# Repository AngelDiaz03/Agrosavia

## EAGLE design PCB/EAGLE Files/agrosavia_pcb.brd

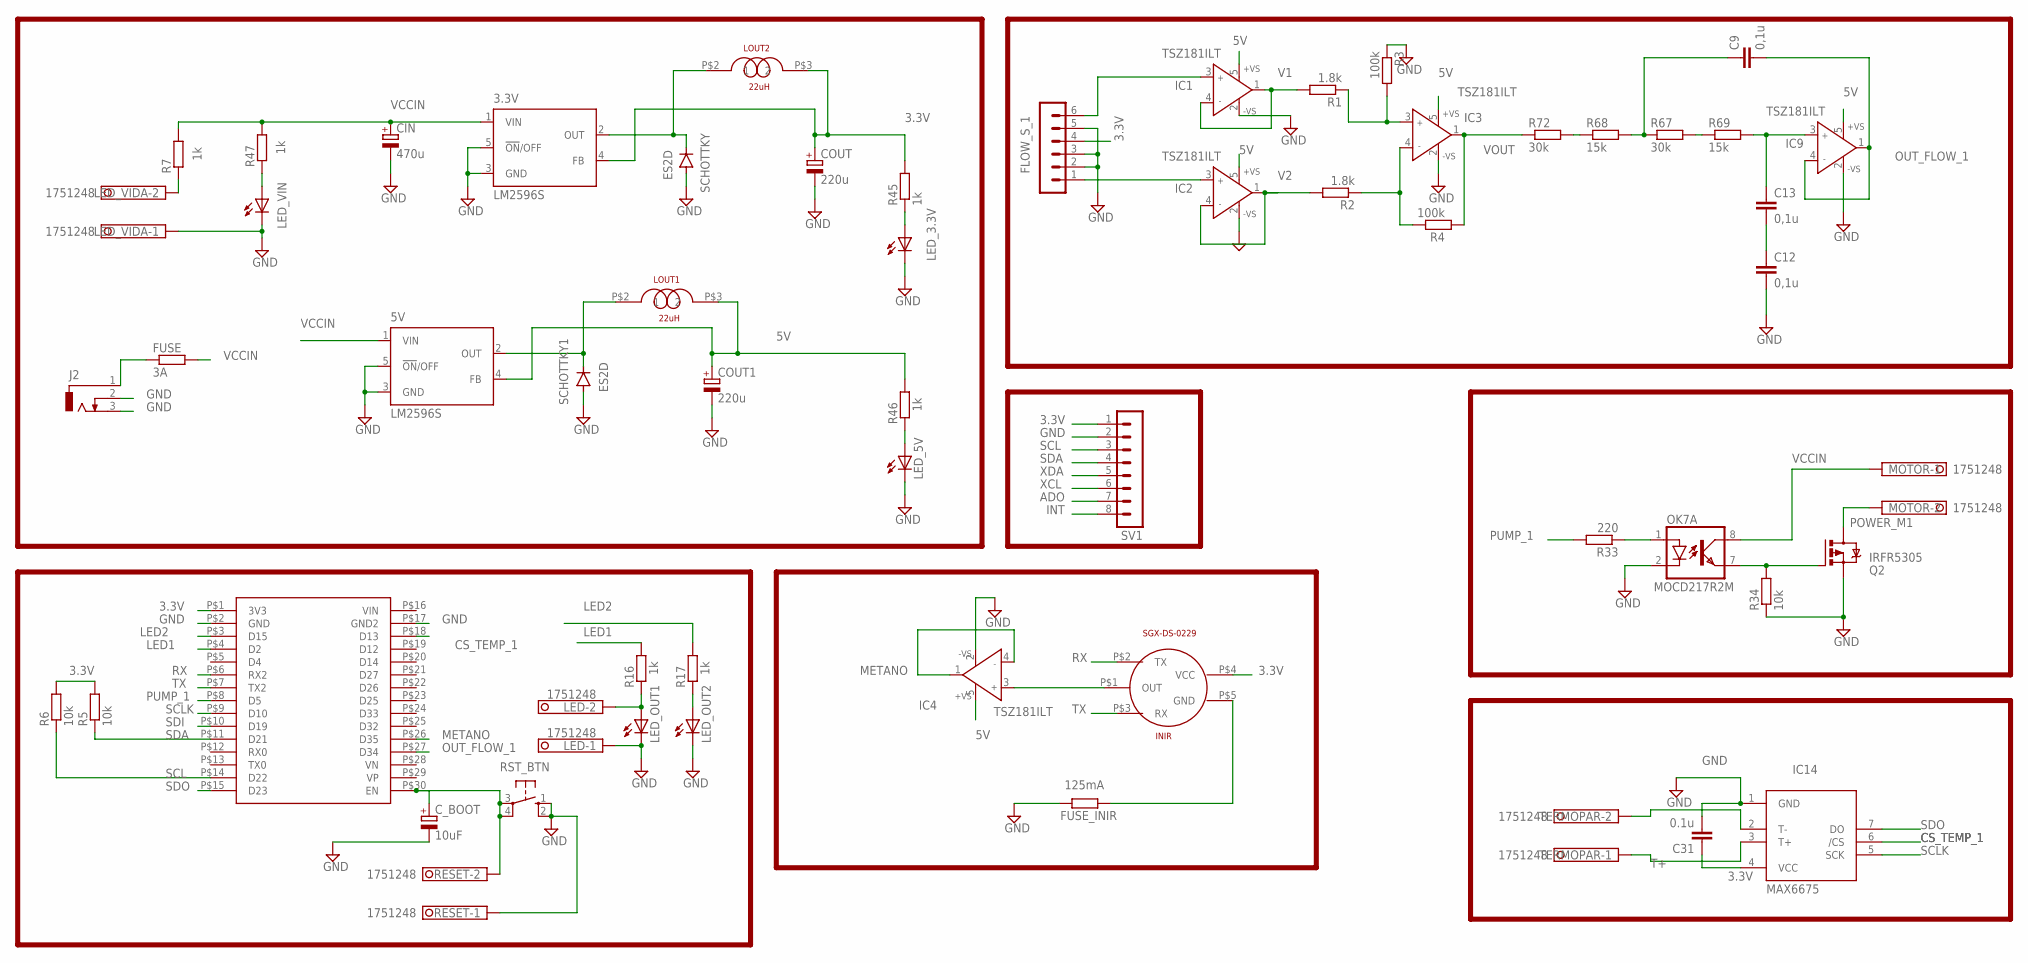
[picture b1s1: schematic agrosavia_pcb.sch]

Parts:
3.3V, 5V: LM2596S; TO263-5
C9, C12, C13: 0,1u; C0805
C31: 0.1u; C0805
CIN: 470u; SANYO-OSCON_SMD_F12
COUT, COUT1: 220u; UD-10X10_NICHICON
C_BOOT: 10uF; SANYO-OSCON_SMD_B6
ESP32DEVKITV1: ESP32
FLOW_S_1: MA06-1
FUSE: 3A; R1206
FUSE_INIR: 125mA; R0402
IC1, IC2, IC3, IC4, IC9: TSZ181ILT; SOT23-5
IC14: MAX6675; SO08
J2: DCJ0303
LED: 1751248
LED_3.3V, LED_5V: LED_E; LED_1206
LED_OUT1, LED_OUT2: LED_E; LED_1206
LED_VIDA: 1751248
LED_VIN: LED_E; LED_1206
LOUT1, LOUT2: 22uH; SRP1038A
MOTOR: 1751248
OK7: MOCD217R2M; SOIC08
Q2: IRFR5305; D-PAK_TO252AA
R1, R2: 1.8k; R0805
R3, R4: 100k; R0805
R5, R6, R34: 10k; R1206
R7, R16, R17, R45, R46, R47: 1k; R0805
R33: 220; R0603
R67, R72: 30k; R0805
R68, R69: 15k; R0805
RESET: 1751248
RST_BTN: 10-XX; B3F-10XX
SCHOTTKY, SCHOTTKY1: ES2D; SMB
SGX-DS-0229: INIR
SV1: MA08-1
TERMOPAR: 1751248

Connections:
3.3V: 3.3V.4 (FB), C31.1, COUT.+, ESP32DEVKITV1.P$1 (3V3), FLOW_S_1.4, IC14.4 (VCC), LOUT2.P$3 (2), R5.2, R6.2, R45.2, SGX-DS-0229.P$4 (VCC), SV1.1
5V: 5V.4 (FB), COUT1.+, IC1.5 (+VS), IC2.5 (+VS), IC3.5 (+VS), IC4.5 (+VS), IC9.5 (+VS), LOUT1.P$3 (2), R46.2
ADO: SV1.7
CS_TEMP_1: ESP32DEVKITV1.P$18 (D13), IC14.6 (/CS)
GND: 3.3V.3 (GND), 3.3V.5 (!ON!/OFF), 5V.3 (GND), 5V.5 (!ON!/OFF), C12.2, C31.2, CIN.-, COUT.-, COUT1.-, C_BOOT.-, ESP32DEVKITV1.P$2 (GND), ESP32DEVKITV1.P$17 (GND2), FLOW_S_1.2, FLOW_S_1.3, FLOW_S_1.5, FUSE_INIR.2, IC1.2 (-VS), IC2.2 (-VS), IC3.2 (-VS), IC4.2 (-VS), IC9.2 (-VS), IC14.1 (GND), J2.2, J2.3, LED.1, LED_3.3V.C, LED_5V.C, LED_OUT1.C, LED_OUT2.C, LED_VIDA.1, LED_VIN.C, OK7.2 (C), Q2.3 (S), R3.1, R34.1, RESET.1, RST_BTN.1 (S), RST_BTN.2 (S1), SCHOTTKY.A, SCHOTTKY1.A, SV1.2
INT: SV1.8
LED1: ESP32DEVKITV1.P$4 (D2), R16.2
LED2: ESP32DEVKITV1.P$3 (D15), R17.2
METANO: ESP32DEVKITV1.P$26 (D35), IC4.1 (OUT), IC4.4 (IN-)
unnamed: FLOW_S_1.1, IC2.3 (IN+)
unnamed: FLOW_S_1.6, IC1.3 (IN+)
unnamed: IC3.3 (IN+), R1.1, R3.2
unnamed: IC3.4 (IN-), R2.1, R4.2
unnamed: FUSE_INIR.1, SGX-DS-0229.P$5 (GND)
unnamed: C_BOOT.+, ESP32DEVKITV1.P$30 (EN), RESET.2, RST_BTN.3, RST_BTN.4 (P1)
unnamed: IC4.3 (IN+), SGX-DS-0229.P$1 (OUT)
unnamed: LED_VIDA.2, R7.1
unnamed: LED.2, LED_OUT1.A, R16.1
unnamed: LED_OUT2.A, R17.1
unnamed: OK7.1 (A), R33.1
unnamed: OK7.7 (EMIT), Q2.1 (G), R34.2
unnamed: 3.3V.2 (OUT), LOUT2.P$2 (1), SCHOTTKY.C
unnamed: 5V.2 (OUT), LOUT1.P$2 (1), SCHOTTKY1.C
unnamed: LED_3.3V.A, R45.1
unnamed: LED_VIN.A, R47.1
unnamed: LED_5V.A, R46.1
unnamed: IC14.2 (T-), TERMOPAR.2
unnamed: FUSE.1, J2.1
unnamed: R68.1, R72.2
unnamed: C9.1, R67.1, R68.2
unnamed: R67.2, R69.1
unnamed: C13.1, IC9.3 (IN+), R69.2
unnamed: C12.1, C13.2
OUT_FLOW_1: C9.2, ESP32DEVKITV1.P$27 (D34), IC9.1 (OUT), IC9.4 (IN-)
POWER_M1: MOTOR.2, Q2.4 (D)
PUMP_1: ESP32DEVKITV1.P$8 (D5), R33.2
RX: ESP32DEVKITV1.P$6 (RX2), SGX-DS-0229.P$2 (TX)
SCL: ESP32DEVKITV1.P$14 (D22), R6.1, SV1.3
SCLK: ESP32DEVKITV1.P$9 (D10), IC14.5 (SCK)
SDA: ESP32DEVKITV1.P$11 (D21), R5.1, SV1.4
SDI: ESP32DEVKITV1.P$10 (D19)
SDO: ESP32DEVKITV1.P$15 (D23), IC14.7 (DO)
T+: IC14.3 (T+), TERMOPAR.1
TX: ESP32DEVKITV1.P$7 (TX2), SGX-DS-0229.P$3 (RX)
V1: IC1.1 (OUT), IC1.4 (IN-), R1.2
V2: IC2.1 (OUT), IC2.4 (IN-), R2.2
VCCIN: 3.3V.1 (VIN), 5V.1 (VIN), CIN.+, FUSE.2, MOTOR.1, OK7.8 (COL), R7.2, R47.2
VOUT: IC3.1 (OUT), R4.1, R72.1
XCL: SV1.6
XDA: SV1.5

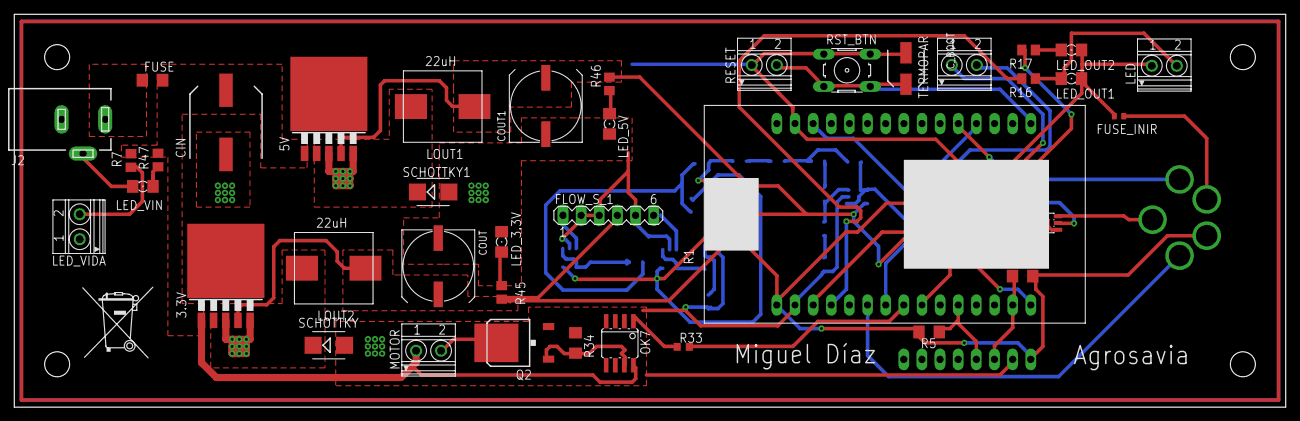
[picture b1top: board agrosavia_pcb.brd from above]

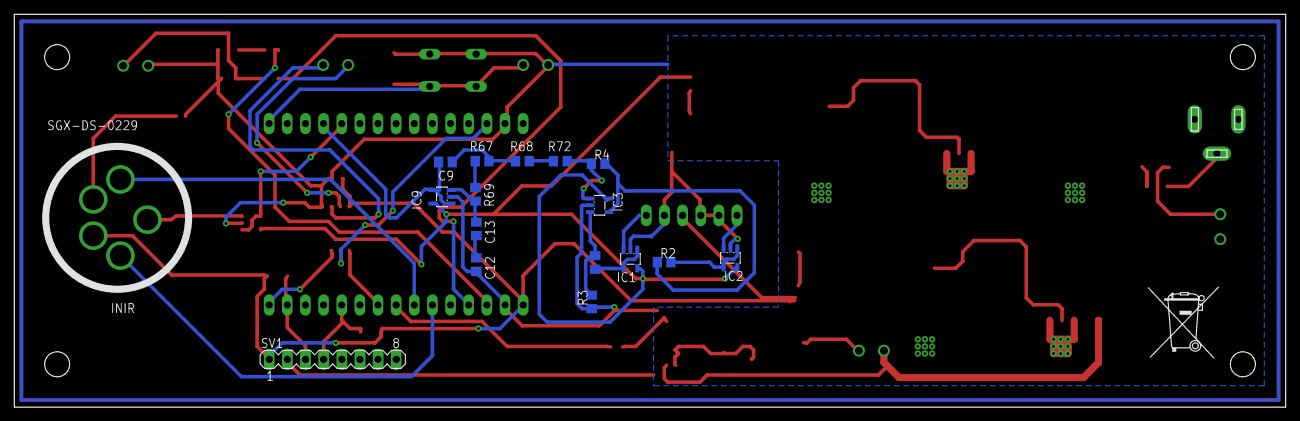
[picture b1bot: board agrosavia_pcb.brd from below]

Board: 2 copper layers, 178.0 x 55.0 mm, 60 parts (17 on the bottom side), 45 nets.

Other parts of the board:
U$3, U$4: MUELLTONNE_10.00

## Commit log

2021-01-10 commit all
2021-01-10 commit all 2
2021-02-13 Final entregado
